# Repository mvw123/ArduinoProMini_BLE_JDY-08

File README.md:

ARDUINO BLE JDY-08 Sensor Node
==============================

Bluetooth temperature sensor node using the JDY-08 bluetooth module which connects to a hub to transfer data onto the internet.

CAD B
=====
NOT RELEASED

* Adding location for +/-0.1Deg C temperature sensor which requires a regulator to be fitted to achieve +/-0.1C. 
* G-NICO-018 (TSYS01) footprint and symbol are from snap EDA

CAD A
=====
WORK IN PROGRESS - This board is not tested in any way shape or form. 

CAD A released for manufacture 8 Nov 2017. 

* Low power battery operated Bluetooth LE environmental sensor node. 
* Based on an Arduino Pro Mini 3.3v, 8MHz device
* Arduino IDE compatible ATMEGA328P, but without the expansion pinouts 
* Using JDY-08 Bluetooth LE CC2541 with FET power down added to PCB for low power modes. 
* Eagle cad 7.5.0
* For use with NON-rechargable batteries eg 2 x AA or AAA 
* Reverse battery protection and safety fuse (battery input only)
* 3V Operation direct from battery, no regulator 

Derived from the Arduino Pro Mini board 3.3v 8MHz version, with BLE added, connectors removed for space and routing reasons. 

Open Source Hardware. 

MVW 

www.guvvy.co.uk

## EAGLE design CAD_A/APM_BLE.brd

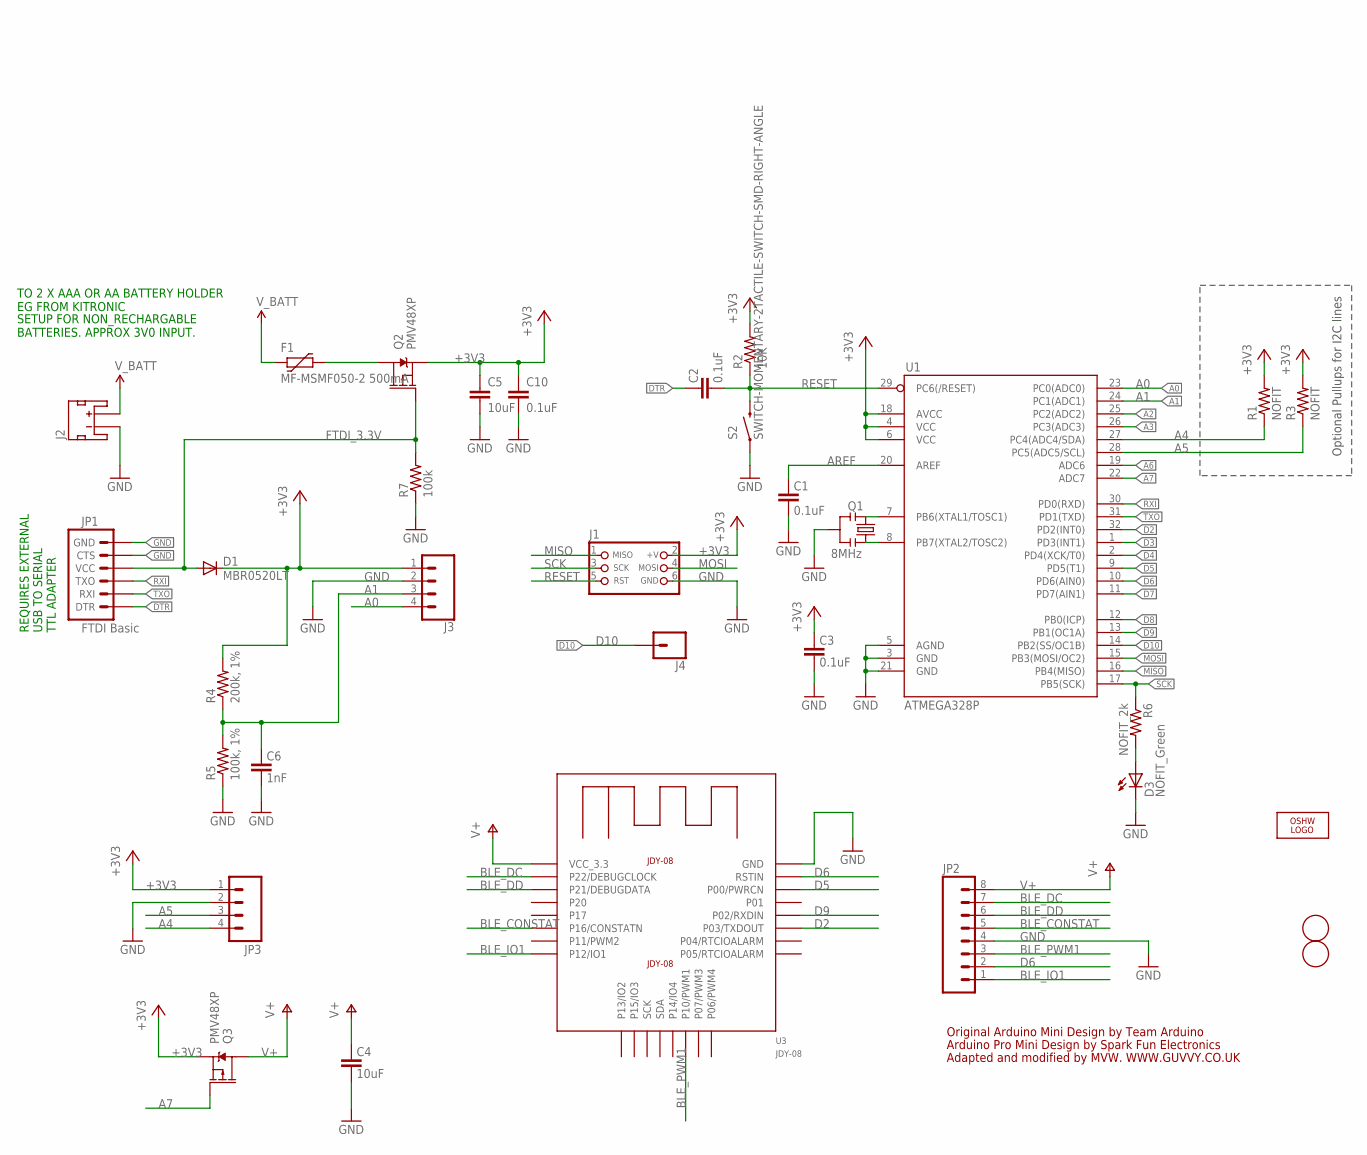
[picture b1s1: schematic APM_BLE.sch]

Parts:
C1, C2, C3, C10: 0.1uF; 0603-CAP
C4: 10uF; 0603-CAP
C5: 10uF; C0805K
C6: 1nF; 0603-CAP
D1: MBR0520LT; SOD123
D3: NOFIT_Green; 0603-LED-ALT1
F1: MF-MSMF050-2 500mA; PTC1812L
FID1, FID2: FIDUCIAL; FIDUCIAL_1MM
J1: CON_HEADER_PRG_AVR_ICSP-PTH; HEADER_PRG_2X03
J2: B2B-PH-K-S(LF)(SN); JST-2-SMD
J3: CONN_04; 1X04
J4: CONN_01; 1X01
JP1: FTDI Basic; 1X06
JP2: M08BM08B-SRSS-TB; BM08B-SRSS-TB
JP3: M04PTH; 1X04
LOGO1: OSHW_LOGO_FILLX0200-NT; OSHW_FILLX200_NOTEXT
Q1: 8MHz; RESONATOR-SMD-1:1
Q2, Q3: PMV48XP; SOT23-3
R1, R3: NOFIT; 0603-RES
R2: 10K; 0603-RES
R4: 200k, 1%; 0603-RES
R5: 100k, 1%; 0603-RES
R6: NOFIT_2k; 0603-RES
R7: 100k; 0603-RES
S2: SWITCH-MOMENTARY-2TACTILE-SWITCH-SMD-RIGHT-ANGLE; TACTILE_SWITCH-SMD-RIGHT-ANGLE
U1: ATMEGA328P; TQFP32-08
U3: JDY-08

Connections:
+3V3: C3.2, C5.1, C10.1, D1.C, J1.2 (+V), J3.1, JP3.1, Q2.2 (S), Q3.2 (S), R1.2, R2.2, R3.2, R4.2, U1.4 (VCC), U1.6 (VCC), U1.18 (AVCC)
A0: J3.4, U1.23 (PC0(ADC0))
A1: C6.2, J3.3, R4.1, R5.2, U1.24 (PC1(ADC1))
A2: U1.25 (PC2(ADC2))
A3: U1.26 (PC3(ADC3))
A4: JP3.4, R1.1, U1.27 (PC4(ADC4/SDA))
A5: JP3.3, R3.1, U1.28 (PC5(ADC5/SCL))
A6: U1.19 (ADC6)
A7: Q3.1 (G), U1.22 (ADC7)
AREF: C1.2, U1.20 (AREF)
BLE_CONSTAT: JP2.5, U3.P16/CONSTATN
BLE_DC: JP2.7, U3.P22/DEBUGCLOCK
BLE_DD: JP2.6, U3.P21/DEBUGDATA
BLE_IO1: JP2.1, U3.P12/IO1
BLE_PWM1: JP2.3, U3.P10/PWM1
D2: U1.32 (PD2(INT0)), U3.P03/TXDOUT
D3: U1.1 (PD3(INT1))
D4: U1.2 (PD4(XCK/T0))
D5: U1.9 (PD5(T1)), U3.P00/PWRCN
D6: JP2.2, U1.10 (PD6(AIN0)), U3.RSTIN
D7: U1.11 (PD7(AIN1))
D8: U1.12 (PB0(ICP))
D9: U1.13 (PB1(OC1A)), U3.P02/RXDIN
D10: J4.1, U1.14 (PB2(SS/OC1B))
DTR: C2.2, JP1.1 (DTR)
FTDI_3.3V: D1.A, JP1.4 (VCC), Q2.1 (G), R7.2
GND: C1.1, C3.1, C4.1, C5.2, C6.1, C10.2, D3.C, J1.6 (GND), J2.1 (-), J3.2, JP1.5 (CTS), JP1.6 (GND), JP2.4, JP3.2, Q1.2, R5.1, R7.1, S2.1, U1.3 (GND), U1.5 (AGND), U1.21 (GND), U3.GND
MISO: J1.1 (MISO), U1.16 (PB4(MISO))
MOSI: J1.4 (MOSI), U1.15 (PB3(MOSI/OC2))
unnamed: Q1.3, U1.8 (PB7(XTAL2/TOSC2))
unnamed: Q1.1, U1.7 (PB6(XTAL1/TOSC1))
unnamed: F1.2, Q2.3 (D)
unnamed: D3.A, R6.2
RESET: C2.1, J1.5 (RST), R2.1, S2.2, U1.29 (PC6(/RESET))
RXI: JP1.3 (TXO), U1.30 (PD0(RXD))
SCK: J1.3 (SCK), R6.1, U1.17 (PB5(SCK))
TXO: JP1.2 (RXI), U1.31 (PD1(TXD))
V+: C4.2, JP2.8, Q3.3 (D), U3.VCC_3.3
V_BATT: F1.1, J2.2 (+)

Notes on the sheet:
Original Arduino Mini Design by Team Arduino
Arduino Pro Mini Design by Spark Fun Electronics
Optional Pullups for I2C lines
TO 2 X AAA OR AA BATTERY HOLDER EG FROM KITRONIC
SETUP FOR NON_RECHARGABLE BATTERIES. APPROX 3V0 INPUT.
REQUIRES EXTERNAL USB TO SERIAL TTL ADAPTER
Adapted and modified by MVW. WWW.GUVVY.CO.UK

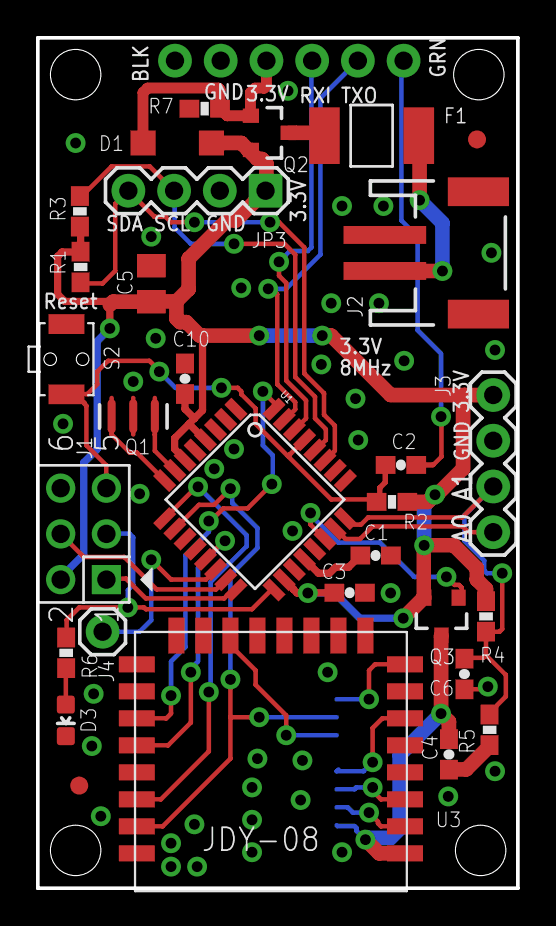
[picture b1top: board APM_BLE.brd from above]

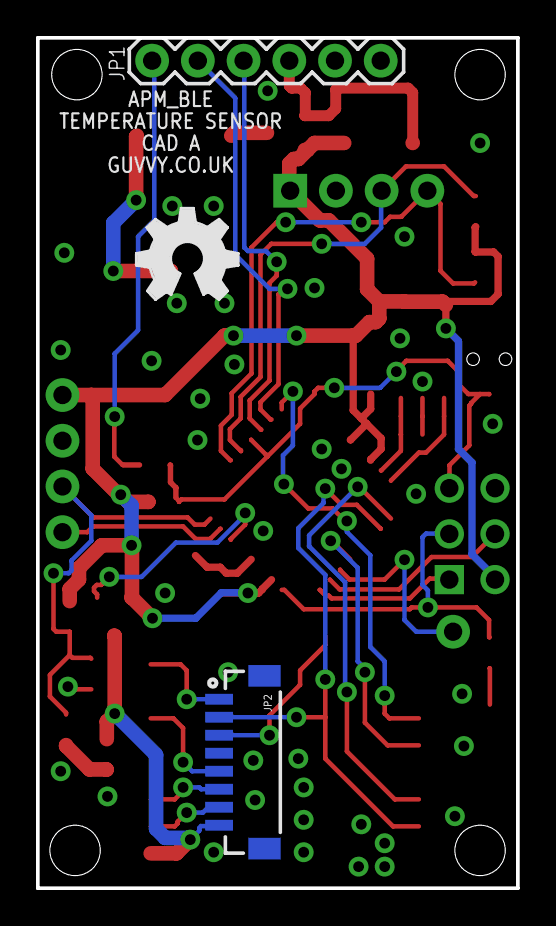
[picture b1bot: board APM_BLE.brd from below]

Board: 2 copper layers, 26.7 x 47.2 mm, 33 parts (3 on the bottom side), 32 nets.

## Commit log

2017-11-08 CAD A first submission
    Changed fiducially and added OSH logo after cad release to OSH park.
    also deleted superfluous text on values layer.
2017-11-08 added readme file
2017-11-08 Update battery voltage sense resistor values
    Update battery voltage sense resistor values
2017-11-08 minor text update
2017-11-08 minor update
2017-11-08 JDY-08 BLE eagle library file
    JDY-08 BLE eagle library file. Not texted or fully checked yet.
2017-11-09 minor updates and file movements
2017-11-09 lib file move
2017-11-16 Latest files
2017-11-26 pnums added and cap change
    Changed 10uF cap to 0603, updated PCB
    added farnell pnums
2018-01-19 Minor updates
    Minor Updates
2019-02-10 unknown changes

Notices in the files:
parts and their libraries:
SparkFun-Aesthetics: Licensing: CC v3.0 Share-Alike You are welcome to use this library for commercial purposes.
SparkFun-Electromechanical: Licensing: Creative Commons ShareAlike 4.0 International - https://creativecommons.org/licenses/by-sa/4.0
